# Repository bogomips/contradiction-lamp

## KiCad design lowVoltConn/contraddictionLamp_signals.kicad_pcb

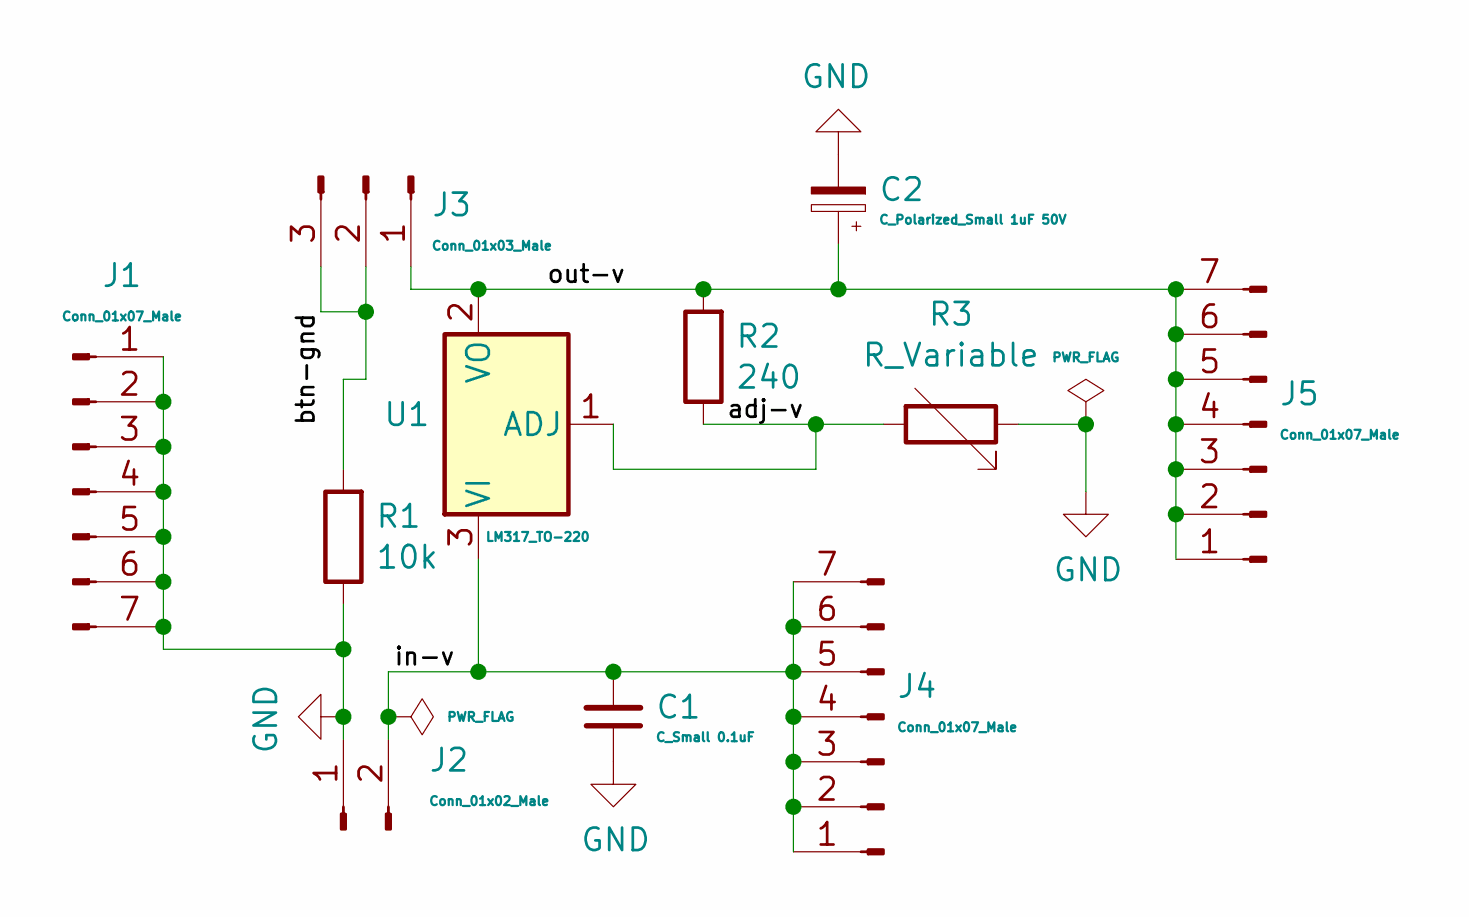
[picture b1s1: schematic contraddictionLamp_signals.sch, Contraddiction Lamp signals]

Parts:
C1: C_Small 0.1uF; C_Disc_D5.1mm_W3.2mm_P5.00mm
C2: C_Polarized_Small 1uF 50V; CP_Radial_D6.3mm_P2.50mm
J1, J4, J5: Conn_01x07_Male; PinHeader_1x07_P2.54mm_Vertical
J2: Conn_01x02_Male; PinHeader_1x02_P2.54mm_Vertical
J3: Conn_01x03_Male; PinHeader_1x03_P2.54mm_Vertical
R1: 10k; R_Axial_DIN0207_L6.3mm_D2.5mm_P7.62mm_Horizontal
R2: 240; R_Axial_DIN0207_L6.3mm_D2.5mm_P7.62mm_Horizontal
R3: R_Variable; Potentiometer_Bourns_3296W_Vertical
U1: LM317_TO-220; TO-220-3_Vertical

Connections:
/adj-v: R2.1, R3.2, U1.1 (ADJ)
/btn-gnd: J3.2, J3.3, R1.2
/in-v: C1.2, J2.2, J4.1, J4.2, J4.3, J4.4, J4.5, J4.6, J4.7, U1.3 (VI)
/out-v: C2.1, J3.1, J5.1, J5.2, J5.3, J5.4, J5.5, J5.6, J5.7, R2.2, U1.2 (VO)
GND: C1.1, C2.2, J1.1, J1.2, J1.3, J1.4, J1.5, J1.6, J1.7, J2.1, R1.1, R3.1

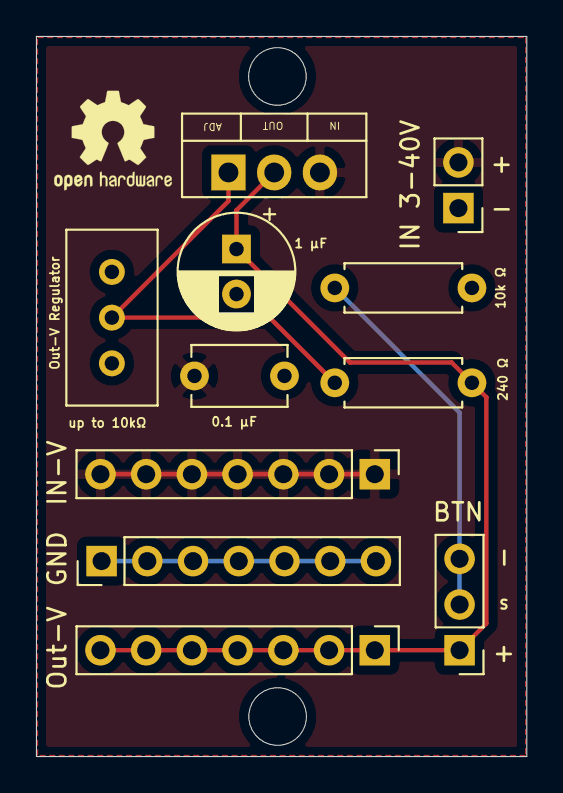
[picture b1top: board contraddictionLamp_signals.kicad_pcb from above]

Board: 2 copper layers, 27.2 x 40.0 mm, 11 parts (0 on the bottom side), 5 nets.

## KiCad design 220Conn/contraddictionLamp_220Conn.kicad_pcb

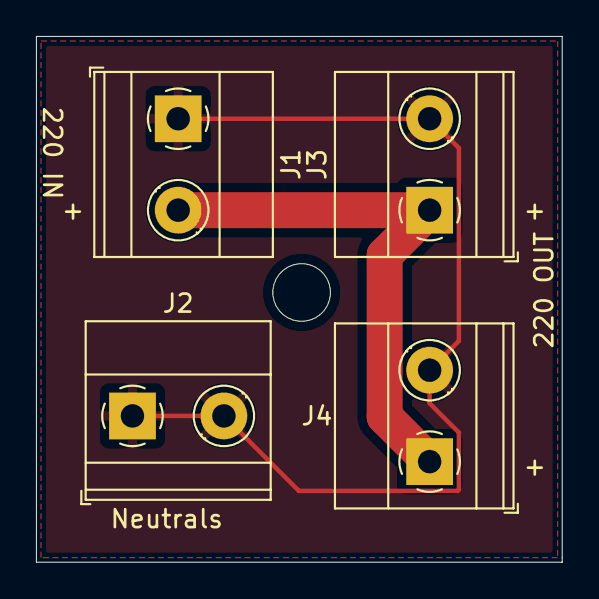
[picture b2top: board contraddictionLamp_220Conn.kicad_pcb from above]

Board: 2 copper layers, 29.2 x 29.2 mm, 4 parts (0 on the bottom side), 2 nets.

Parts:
J1, J2, J3, J4: Screw_Terminal_01x02; TerminalBlock_Phoenix_MKDS-1,5-2-5.08_1x02_P5.08mm_Horizont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

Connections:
/Line: J1.2, J3.1, J4.1
/Neutral: J1.1, J2.1, J2.2, J3.2, J4.2
